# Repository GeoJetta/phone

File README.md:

# phone.

## The quintessential dumb phone.
No distractions, in a satisfyingly tiny package.

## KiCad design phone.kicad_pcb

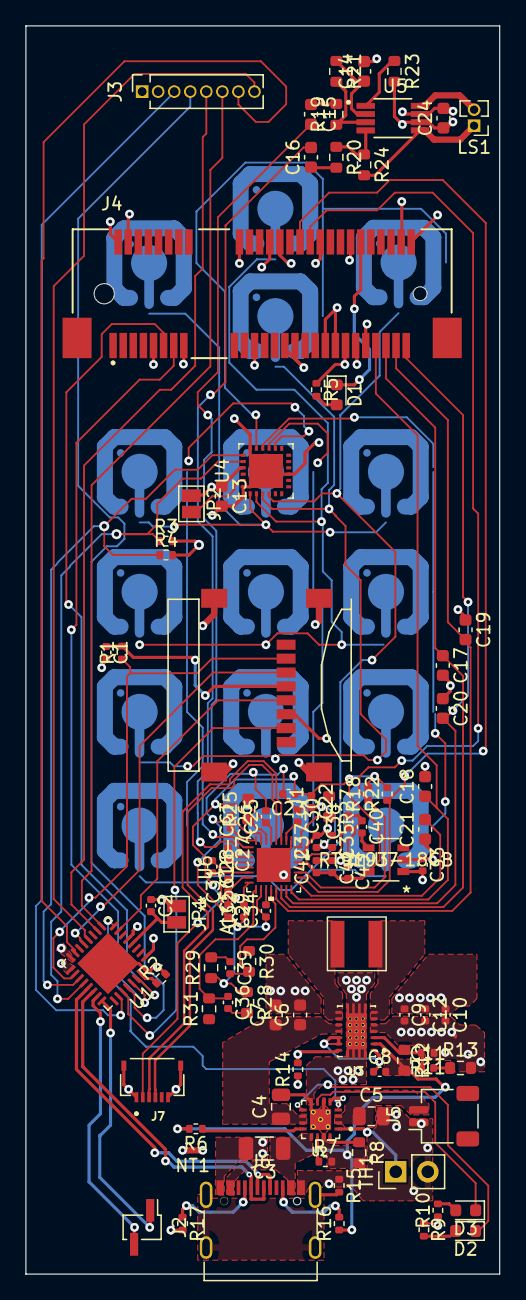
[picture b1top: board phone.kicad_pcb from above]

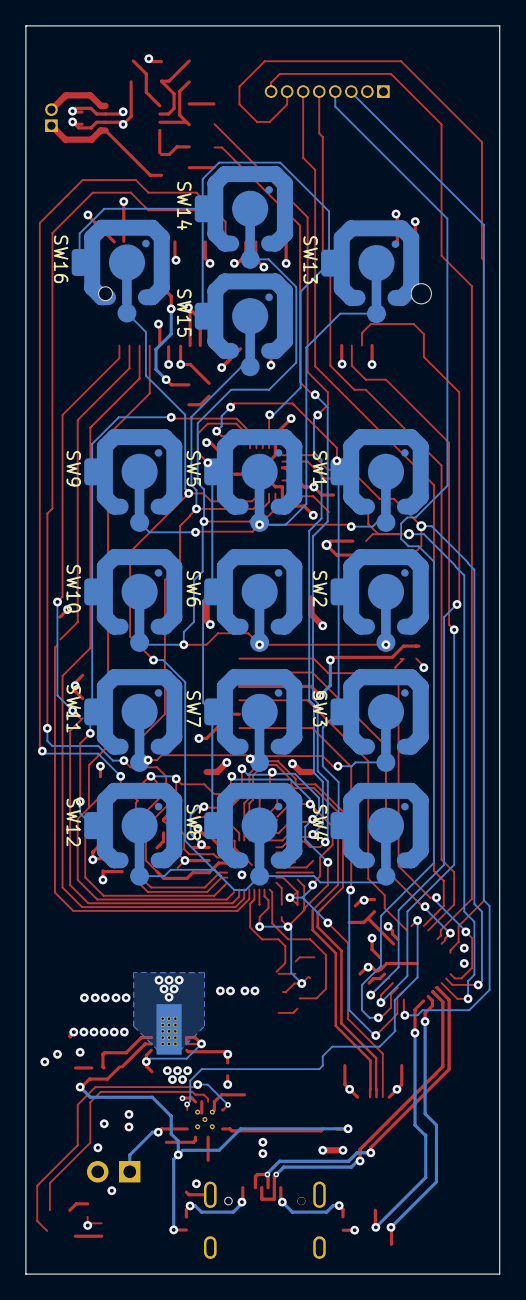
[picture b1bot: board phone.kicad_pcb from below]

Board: 4 copper layers, 37.5 x 98.8 mm, 112 parts (16 on the bottom side), 92 nets.

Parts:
C1: 10uF; C_0402_1005Metric
C2: 100nF; C_0402_1005Metric
C3: 1uF X7R; C_1206_3216Metric
C4, C5: 4.7uF X5R; C_0805_2012Metric
C6, C7: 10uF X5R; C_0603_1608Metric
C8: 100nF X5/7R; C_0402_1005Metric
C9, C10, C12: 22uF X5R; C_0402_1005Metric
C11: 4.7pF; C_0402_1005Metric
C13: 1uF; C_0603_1608Metric
C14, C24: 1uF 6.3V; C_0603_1608Metric
C15, C16: 100nF 6.3V; C_0603_1608Metric
C17, C18, C19, C20, C21: NC 22pF 6.3V; C_0603_1608Metric
C22, C29, C35, C36, C39, C41: 100nF 6.3V; C_0402_1005Metric
C23, C25, C26, C31, C37: 4.7uF 6.3V; C_0402_1005Metric
C27, C28, C30, C32, C34, C38, C42: 2.2uF 6.3V; C_0402_1005Metric
C33, C43: 1uF X7R; C_0402_1005Metric
C40: 22nF; C_0402_1005Metric
D1: LED; LED_0603_1608Metric
D2: GREEN LED; LED_0603_1608Metric
D3: YELLOW LED; LED_0603_1608Metric
J1: 47219-2001; MOLEX_47219-2001
J2: SWDIO; PinSocket_1x02_P1.27mm_Vertical_SMD_Pin1Left
J3: Display; PinSocket_1x08_P1.27mm_Vertical
J4: Bus_PCI_Express_Mini; MOLEX_67910-5700
J5: Battery; JST_SH_SM02B-SRSS-TB_1x02-1MP_P1.00mm_Horizontal
J6: USB_C_Receptacle_USB2.0; SOFNG_MC-311D
J7: FH34SRJ-6S-0.5SH(50); HRS_FH34SRJ-6S-0.5SH(50)
JP1, JP2: SolderJumper_2_Open; SolderJumper-2_P1.3mm_Open_Pad1.0x1.5mm
L1: 1.5uH; MPIT4030
LS1: Earphone; PinHeader_1x02_P1.27mm_Vertical
NT1: NetTie_2; NetTie-2_SMD_Pad0.5mm
R1, R2, R18, R22: 10k; R_0402_1005Metric
R3, R4: 4.7k; R_0402_1005Metric
R5, R10: 68; R_0402_1005Metric
R6, R7: 46.4k; R_0402_1005Metric
R8: 910; R_0603_1608Metric
R9: 1; R_0402_1005Metric
R11, R14, R15: 1M; R_0402_1005Metric
R12, R13: 180k; R_0603_1608Metric
R16, R17: 5.11k; R_0402_1005Metric
R19, R20, R21, R23, R24: 20k; R_0603_1608Metric
R25: 47; R_0603_1608Metric
R27: 0; R_0603_1608Metric
R28, R29: 22; R_0603_1608Metric
R30, R31: 33; R_0603_1608Metric
SW1: 1; snap dome
SW2: 4; snap dome
SW3: 7; snap dome
SW4: *; snap dome
SW5: 2; snap dome
SW6: 5; snap dome
SW7: 8; snap dome
SW8: 0; snap dome
SW9: 3; snap dome
SW10: 6; snap dome
SW11: 9; snap dome
SW12: #; snap dome
SW13: End/Back; snap dome
SW14: Up; snap dome
SW15: Down; snap dome
SW16: Call/OK; snap dome
TH1: Thermistor_NTC; PinHeader_1x02_P2.54mm_Vertical
U1: STM32L432KCUx; QFN-32-1EP_5x5mm_P0.5mm_EP3.45x3.45mm
U2: BQ24072RGTT; IC_BQ24072RGTT
U3: TPS63020DSJR; IC_TPS63020DSJR
U4: AW9523BTQR; QFN-24_EP_4x4_Pitch0.5mm
U5: LM4889MM
U6: ALC5616-CGT
U7: RT9193-18GB

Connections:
+3V3: C1.1, C9.2, C10.2, C12.2, C13.1, C24.1, C33.2, C35.1, C37.2, J1.4 (VDD), J3.1, J4.2 (+3V3AUX), J4.24 (+3V3AUX), J4.39 (+3V3AUX), J4.41 (+3V3AUX), J4.52 (+3V3AUX), JP2.1 (A), R1.2, R3.2, R4.2, R5.1, R9.1, R10.1, R11.1, R13.2, R14.1, R23.2, U1.1 (VDD), U1.5 (VDDA), U1.17 (VDD), U2.5 (EN2), U3.4 (VOUT_4), U3.5 (VOUT_5), U4.21 (VCC), U5.6 (VDD), U6.31 (MICVDD), U7.1 (VIN)
+5V: C3.1, J6.A4 (VBUS), J6.A9 (VBUS), J6.B4 (VBUS), J6.B9 (VBUS), U2.13 (IN)
/BL_TFT: J3.8, U1.12 (PA6)
/CE_PWR: U1.8 (PA2), U2.4 (~CE)
/CHG_PWR: D2.1 (K), U2.9 (~CHG)
/CS_TFT: J3.5, U1.10 (PA4)
/DC_TFT: J3.7, U1.15 (PB1)
/MCU_D+: J6.A7 (D-), J6.B7 (D-), U1.22 (PA12)
/MCU_D-: J6.A6 (D+), J6.B6 (D+), U1.21 (PA11)
/MISO_SD: J1.7 (DAT0), U1.27 (PB4)
/MOSI_SD: J1.3 (CMD), U1.13 (PA7)
/MOSI_TFT: J3.4, U1.28 (PB5)
/PCM_CLK: C18.1, J4.45 (Reserved), U6.24 (BCLK1)
/PCM_DIN: C19.2, J4.49 (Reserved), U6.21 (ADCDAT1)
/PCM_DOUT: C17.1, J4.47 (Reserved), U6.22 (DACDAT1)
/PCM_SYNC: C20.2, J4.51 (Reserved), U6.23 (LRCK1)
/PG_BATT: D3.1 (K), U2.7 (~PGOOD)
/PG_PWR: R14.2, U3.14 (PG)
/RST_TFT: J3.6, U1.9 (PA3)
/SCL: R4.1, U1.19 (PA9), U4.19 (SCL)
/SCLK_SD: J1.5 (CLK), U1.7 (PA1)
/SCLK_TFT: J3.3, U1.26 (PB3)
/SDA: R3.1, U1.20 (PA10), U4.20 (SDA)
/SWCLK: J2.1, U1.24 (PA14)
/SWDIO: J2.2, U1.23 (PA13)
/UART_RX: J4.11 (REFCLK-), U1.30 (PB7)
/UART_TX: J4.13 (REFCLK+), U1.29 (PB6)
/audio/AMP_OFF: R23.1, U5.1 (~SHDN)
/audio/IN+: C15.2, U6.9 (LOUTL/P)
/audio/IN-: C16.2, U6.10 (LOUTR/N)
/audio/MCLK: C21.2, U6.25 (MCLK)
/audio/OUT2+: J7.3 (OUT+), U6.3 (IN2P)
/audio/OUT2-: J7.4 (OUT-), U6.4 (IN2N/JD2)
/audio/SCL: J4.30 (SMB_CLK), R22.1, U6.26 (SCL)
/audio/SDA: J4.32 (SMB_DATA), R18.1, U6.27 (SDA)
/keypad/H1: SW1.2, SW5.2, SW9.2, SW13.2, U4.1 (P1_0)
/keypad/H2: SW2.2, SW6.2, SW10.2, SW14.2, U4.2 (P1_1)
/keypad/H3: SW3.2, SW7.2, SW11.2, SW15.2, U4.3 (P1_2)
/keypad/H4: SW4.2, SW8.2, SW12.2, SW16.2, U4.4 (P1_3)
/keypad/RST_GPIO: JP2.2 (B), U4.23 (RSTN)
/keypad/V1: SW1.1, SW2.1, SW3.1, SW4.1, U4.14 (P1_4)
/keypad/V2: SW5.1, SW6.1, SW7.1, SW8.1, U4.15 (P1_5)
/keypad/V3: SW9.1, SW10.1, SW11.1, SW12.1, U4.16 (P1_6)
/keypad/V4: SW13.1, SW14.1, SW15.1, SW16.1, U4.17 (P1_7)
/~CS_SD: J1.2 (CD/DAT3), R1.1, U1.18 (PA8)
DBVDD: C22.1, C23.1, C29.1, C31.1, C41.2, C42.1, C43.2, J7.2 (VDD), R18.2, R22.2, R25.1, U6.6 (AVDD), U6.15 (CPVDD), U6.29 (DBVDD), U7.5 (VOUT)
GND: C1.2, C2.1, C8.2, C13.2, C14.2, C17.2, C18.2, C19.1, C20.1, C21.1, C24.2, C33.1, C38.2, C40.1, C41.1, C42.2, C43.1, J1.6 (VSS), J1.G1 (GND@1), J1.G2 (GND@2), J1.G3 (GND@3), J1.G4 (GND@4), J3.2, J4.4 (GND), J4.9 (GND), J4.15 (GND), J4.18 (GND), J4.21 (GND), J4.26 (GND), J4.27 (GND), J4.29 (GND), J4.34 (GND), J4.35 (GND), J4.37 (GND), J4.40 (GND), J4.43 (GND), J4.50 (GND), J7.1 (GND), J7.6 (GND), J7.S1 (SHIELD), J7.S2 (SHIELD), JP1.1 (A), NT1.2, R2.2, R6.2, R7.2, R8.2, R12.2, R16.1, R17.2, U1.16 (VSS), U1.32 (VSS), U1.33 (VSS), U2.15 (TD), U3.2 (GND), U4.9 (GND), U4.18 (AD0), U4.24 (AD1), U4.25 (GND), U5.7 (GND), U6.1 (JD1), U6.33 (CPGND/DGND), U7.2 (GND)
GNDA: C22.2, C23.2, C25.2, C26.1, C29.2, C30.1, C31.2, C32.1, C34.1, C35.2, C37.1, R28.1, R29.1, U6.7 (AGND), U6.18 (CPVREF)
GNDPWR: C3.2, C4.2, C5.2, C6.2, C7.2, C9.1, C10.1, C12.1, J5.1, J6.A1 (GND), J6.A12 (GND), J6.B1 (GND), J6.B12 (GND), NT1.1, R15.1, TH1.2, U2.6 (EN1), U2.8 (VSS), U2.17 (EXP), U3.15 (PGND)
unnamed: C2.2, JP1.2 (B), U1.4 (NRST)
unnamed: C4.1, C6.1, C7.1, U2.10 (OUT), U2.11 (OUT), U3.10 (VIN_10), U3.11 (VIN_11)
unnamed: C5.1, J5.2, U2.2 (BAT), U2.3 (BAT)
unnamed: C8.1, U3.1 (VINA), U3.12 (EN), U3.13 (PS/SYNC)
unnamed: C11.1, R11.2, R12.1, U3.3 (FB)
unnamed: C11.2, R13.1
unnamed: C14.1, R21.1, U5.2 (BYPASS)
unnamed: C15.1, R19.2
unnamed: C16.1, R20.2
unnamed: C25.1, R25.2, U6.5 (DACREF)
unnamed: C26.2, U6.8 (VREF)
unnamed: C27.1, U6.11 (CPN2)
unnamed: C27.2, U6.12 (CPP2)
unnamed: C28.1, U6.13 (CPN1)
unnamed: C28.2, U6.14 (CPP1)
unnamed: C30.2, U6.2 (IN1P)
unnamed: C32.2, U6.16 (CPVPP)
unnamed: C34.2, U6.19 (CPVEE)
unnamed: C36.1, R31.2, U6.17 (HPO_R)
unnamed: C36.2, R28.2
unnamed: C38.1, U6.30 (DCVDD)
unnamed: C39.1, R29.2
unnamed: C39.2, R30.2, U6.20 (HPO_L)
unnamed: C40.2, U7.4 (BP)
unnamed: D1.1 (K), J4.42 (~LED_WWAN)
unnamed: D1.2 (A), R5.2
unnamed: D2.2 (A), R9.2
unnamed: D3.2 (A), R10.2
unnamed: J6.A5 (CC1), R17.1
unnamed: J6.B5 (CC2), R16.2
unnamed: J6.S1 (SHIELD), R15.2
unnamed: L1.1, U3.8 (L1_8), U3.9 (L1_9)
unnamed: L1.2, U3.6 (L2_6), U3.7 (L2_7)
unnamed: LS1.1 (-), R24.2, U5.5 (VO1)
unnamed: LS1.2 (+), U5.8 (VO2)
unnamed: R2.1, U1.31 (PH3)
unnamed: R6.1, U2.12 (ILIM)
unnamed: R7.1, U2.14 (TMR)
unnamed: R8.1, U2.16 (ISET)
unnamed: R19.1, R21.2, U5.3 (+IN)
unnamed: R20.1, R24.1, U5.4 (-IN)
unnamed: R27.2, U6.32 (MICBIAS1)
unnamed: TH1.1, U2.1 (TS)

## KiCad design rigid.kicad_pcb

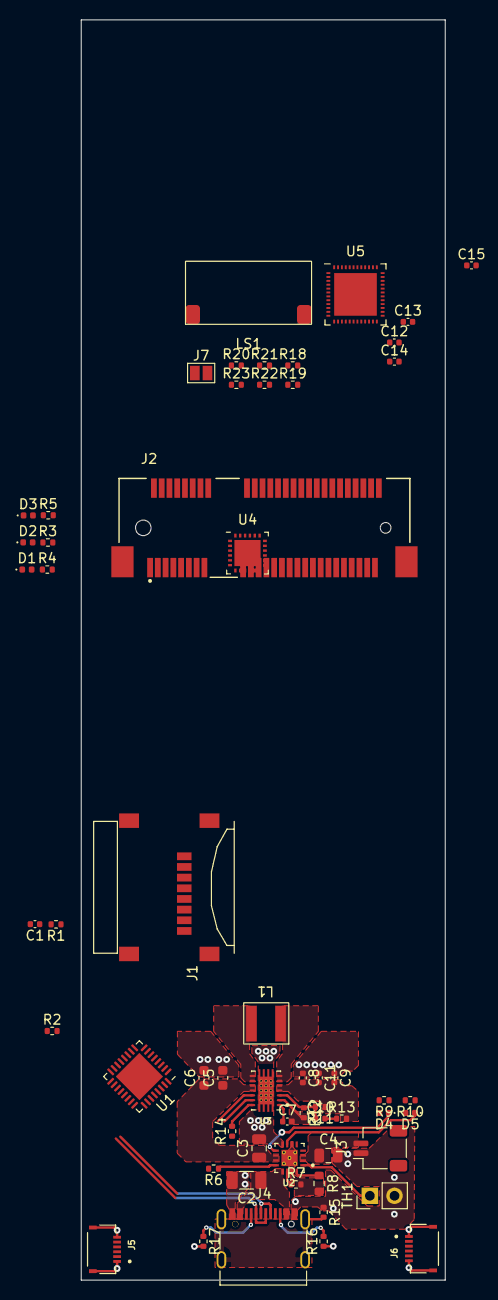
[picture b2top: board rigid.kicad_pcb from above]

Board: 4 copper layers, 37.5 x 130.0 mm, 58 parts (0 on the bottom side), 55 nets.

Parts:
C1: 10uF; C_0402_1005Metric
C2: 1uF X5R; C_1206_3216Metric
C3, C4: 4.7uF X5R; C_0805_2012Metric
C5, C6: 10uF X5R; C_0603_1608Metric
C7: 100nF X5/7R; C_0402_1005Metric
C8, C9, C11: 22uF X5R; C_0402_1005Metric
C10: 4.7pF; C_0402_1005Metric
C12, C13: 1uF; C_0402_1005Metric
C14, C15: 1nF; C_0402_1005Metric
D1, D2, D3, D4, D5: LED; LED_0402_1005Metric
J1: 47219-2001; MOLEX_47219-2001
J2: Bus_PCI_Express_Mini; MOLEX_67910-5700
J3: Battery; JST_SH_SM02B-SRSS-TB_1x02-1MP_P1.00mm_Horizontal
J4: USB_C_Receptacle_USB2.0; SOFNG_MC-311D
J5, J6: FH34SRJ-6S-0.5SH(50); HRS_FH34SRJ-6S-0.5SH(50)
J7: Conn_01x02_Female; SolderJumper-2_P1.3mm_Open_Pad1.0x1.5mm
L1: 1.5uH; MPIT4030
LS1: Earphone; speakerpads
R1, R2, R22, R23: 10k; R_0402_1005Metric
R3, R4, R5: 470; R_0402_1005Metric
R6, R7: 46.4k; R_0402_1005Metric
R8: 910; R_0603_1608Metric
R9, R10: 1.5k; R_0402_1005Metric
R11, R14, R15: 1M; R_0402_1005Metric
R12, R13: 180k; R_0402_1005Metric
R16, R17: 5.11k; R_0402_1005Metric
R18, R19: 22; R_0402_1005Metric
R20, R21: 1k; R_0402_1005Metric
TH1: Thermistor_NTC; PinHeader_1x02_P2.54mm_Vertical
U1: STM32L432KCUx; QFN-32-1EP_5x5mm_P0.5mm_EP3.45x3.45mm
U2: BQ24072RGTT; IC_BQ24072RGTT
U3: TPS63020DSJR; IC_TPS63020DSJR
U4: AW9523BTQR; QFN-24_EP_4x4_Pitch0.5mm
U5: ALC5672; ALC5672-VB-CGT_QFN-48_EP_6x6_Pitch0.4mm

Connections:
+3V3: C1.1, C8.2, C9.2, C11.2, J1.4 (VDD), J2.2 (+3V3AUX), J2.24 (+3V3AUX), J2.39 (+3V3AUX), J2.41 (+3V3AUX), J2.52 (+3V3AUX), R1.2, R11.1, R13.2, R14.1, U1.1 (VDD), U1.5 (VDDA), U1.17 (VDD), U2.5 (EN2), U3.4 (VOUT_4), U3.5 (VOUT_5), U4.21 (VCC)
+5V: C2.1, J4.A4 (VBUS), J4.A9 (VBUS), J4.B4 (VBUS), J4.B9 (VBUS), U2.13 (IN)
/Power/CHG: D4.1 (K), U2.9 (~CHG)
/Power/PG_BATT: D5.1 (K), U2.7 (~PGOOD)
/Power/PG_PS: R14.2, U3.14 (PG)
/~CS_SD: J1.2 (CD/DAT3), R1.1
DBVDD: J5.2 (VDD), J6.2 (VDD), R22.2, R23.2, U5.2 (DBVDD)
GND: C1.2, C7.2, C14.2, C15.2, D1.1 (K), D2.1 (K), D3.1 (K), J1.6 (VSS), J1.G1 (GND@1), J1.G2 (GND@2), J1.G3 (GND@3), J1.G4 (GND@4), J2.4 (GND), J2.9 (GND), J2.15 (GND), J2.18 (GND), J2.21 (GND), J2.26 (GND), J2.27 (GND), J2.29 (GND), J2.34 (GND), J2.35 (GND), J2.37 (GND), J2.40 (GND), J2.43 (GND), J2.50 (GND), J5.1 (GND), J5.6 (GND), J5.S1 (SHIELD), J5.S2 (SHIELD), J6.1 (GND), J6.6 (GND), J6.S1 (SHIELD), J6.S2 (SHIELD), R2.2, R6.2, R7.2, R8.2, R12.2, R16.1, R17.2, U1.16 (VSS), U1.32 (VSS), U1.33 (VSS), U2.6 (EN1), U2.15 (TD), U2.17 (EXP), U2.19, U2.21, U3.2 (GND), U4.9 (GND), U4.18 (AD0), U4.24 (AD1), U4.25 (GND), U5.46 (SPKGNDR), U5.49 (SHIELD)
GNDA: U5.10 (AGND), U5.24 (CPGND)
GNDPWR: C2.2, C3.2, C4.2, C5.2, C6.2, C8.1, C9.1, C11.1, J3.1, J4.A1 (GND), J4.A12 (GND), J4.B1 (GND), J4.B12 (GND), R15.1, TH1.2, U2.8 (VSS), U3.15 (PGND), U3.16, U3.17, U3.18
unnamed: C3.1, C5.1, C6.1, R9.1, R10.1, U2.10 (OUT), U2.11 (OUT), U3.10 (VIN_10), U3.11 (VIN_11)
unnamed: C4.1, J3.2, U2.2 (BAT), U2.3 (BAT)
unnamed: C7.1, U3.1 (VINA), U3.12 (EN), U3.13 (PS/SYNC)
unnamed: C10.1, R11.2, R12.1, U3.3 (FB)
unnamed: C10.2, R13.1
unnamed: C12.1, R18.2
unnamed: C12.2, J7.1
unnamed: C13.1, R19.2
unnamed: C13.2, J7.2
unnamed: C14.1, LS1.2 (+), U5.44 (SPO_RN), U5.48 (SPO_LN)
unnamed: C15.1, LS1.1 (-), R20.2, R21.2
unnamed: D1.2 (A), R4.1
unnamed: D2.2 (A), R3.1
unnamed: D3.2 (A), R5.2
unnamed: D4.2 (A), R9.2
unnamed: D5.2 (A), R10.2
unnamed: J2.42 (~LED_WWAN), R5.1
unnamed: J2.44 (~LED_WLAN), R3.2
unnamed: J2.46 (~LED_WPAN), R4.2
unnamed: J4.A5 (CC1), R17.1
unnamed: J4.B5 (CC2), R16.2
unnamed: J4.S1 (SHIELD), R15.2
unnamed: J5.3 (OUT+), U5.11 (IN1P_RING2)
unnamed: J5.4 (OUT-), U5.12 (IN1N_SLEEVE)
unnamed: J6.3 (OUT+), U5.4 (IN2P/INL1)
unnamed: J6.4 (OUT-), U5.5 (IN2N/INR1)
unnamed: L1.1, U3.8 (L1_8), U3.9 (L1_9)
unnamed: L1.2, U3.6 (L2_6), U3.7 (L2_7)
unnamed: R2.1, U1.31 (PH3)
unnamed: R6.1, U2.12 (ILIM)
unnamed: R7.1, U2.14 (TMR)
unnamed: R8.1, U2.16 (ISET)
unnamed: R18.1, U5.28 (LOUTL/P)
unnamed: R19.1, U5.29 (LOUTR/N)
unnamed: R20.1, U5.1 (SPO_LP)
unnamed: R21.1, U5.45 (SPO_RP)
unnamed: TH1.1, U2.1 (TS)
SCL_CODEC: R23.1, U5.39 (SCL)
SDA_CODEC: R22.1, U5.40 (SDA)
UART_CTS: J2.23 (PERn0), U1.6 (PA0)
UART_RTS: J2.25 (PERp0), U1.7 (PA1)
UART_RX: J2.11 (REFCLK-), U1.9 (PA3)
UART_TX: J2.13 (REFCLK+), U1.8 (PA2)
USB_D+: J4.A6 (D+), J4.B6 (D+), U1.22 (PA12)
USB_D-: J4.A7 (D-), J4.B7 (D-), U1.21 (PA11)

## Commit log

2022-09-08 USB IC Removal
2022-09-09 One piece board, a bit into PCB
2022-09-10 Audio near completion
2022-09-14 All Routed!
2022-09-14 Add gitignore, fix some things
2022-09-14 Pre ignore update
2022-09-14 .gitignore is now working
2022-09-21 Before Shortening
2022-09-22 New Audio
2022-09-25 Getting There
    Need to move keyboard down and finish routing to audio, then we're there!
2022-10-09 First JLCPCB Ship!

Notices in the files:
parts and their libraries:
Copyright 2021 Accelerated Designs. All rights reserved.
